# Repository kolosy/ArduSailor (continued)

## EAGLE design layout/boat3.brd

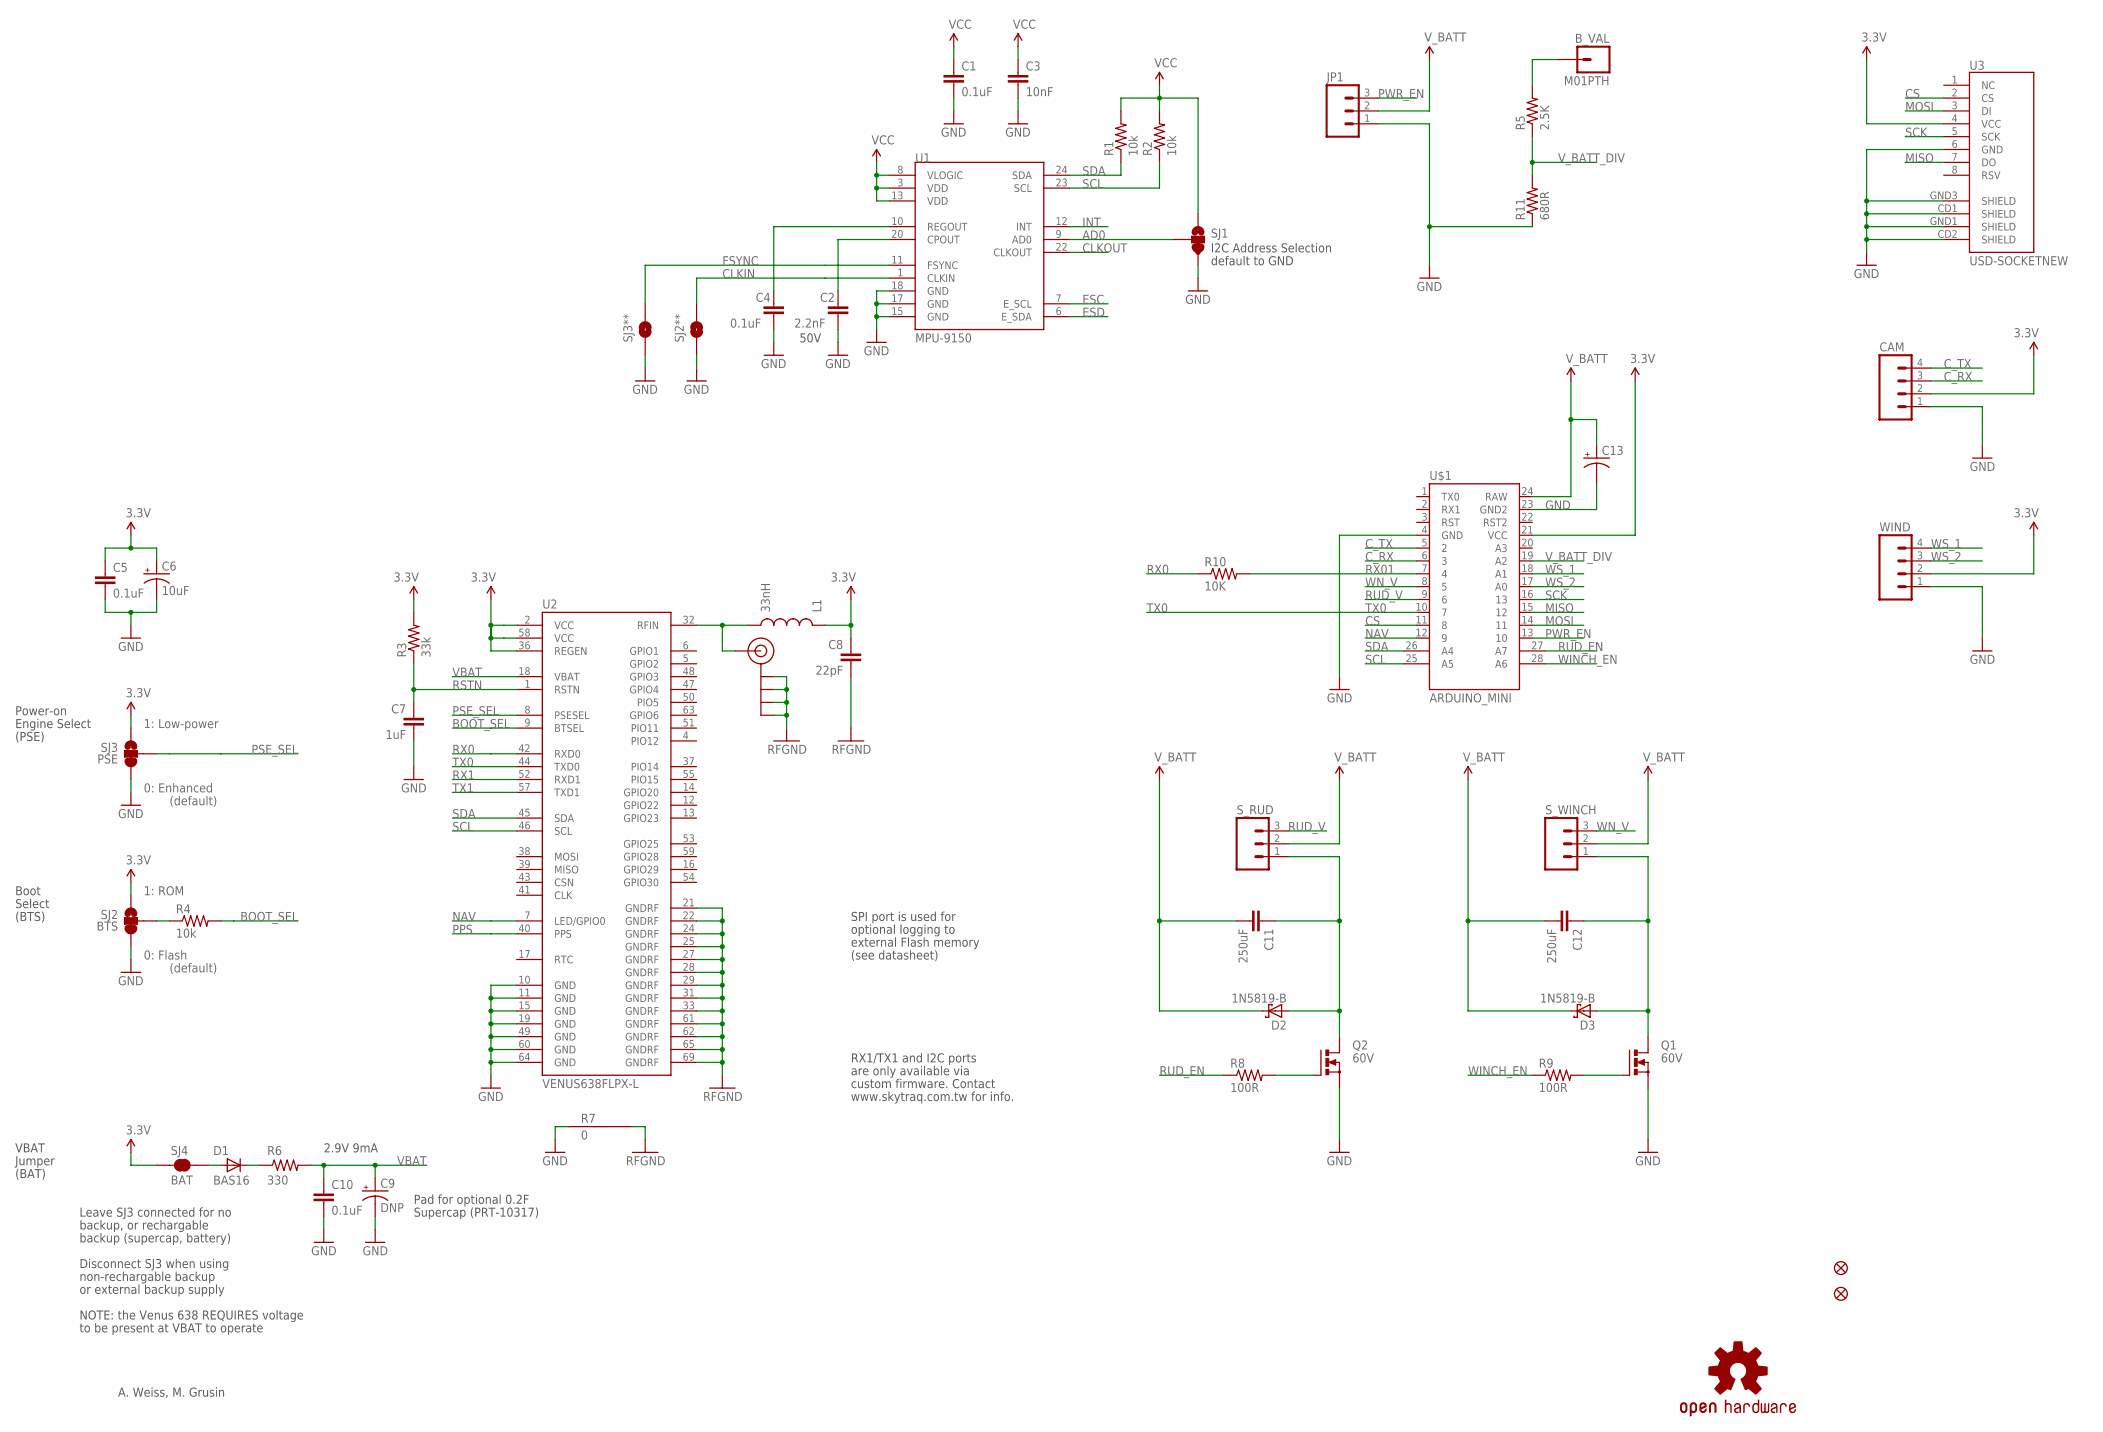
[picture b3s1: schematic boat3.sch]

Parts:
B_VAL: M01PTH; 1X01
C1, C4, C5, C10: 0.1uF; 0402-CAP
C2: 2.2nF; 0402-CAP
C3: 10nF; 0402-CAP
C6: 10uF; EIA3216
C7: 1uF; 0402-CAP
C8: 22pF; 0402-CAP
C9: DNP; CPOL-RADIAL-1000UF-25V
C11, C12: 250uF; CAP-PTH-5MM
C13: CAP_POLPTH4; CPOL-RADIAL-1000UF-25V
CAM: M04PTH; 1X04
D1: BAS16; SOD-323
D2, D3: 1N5819-B; DO41-7.6
JP1: M03SCREW; SCREWTERMINAL-3.5MM-3
JP5: SMA_EDGE; SMA-EDGE
JP7, JP8: FIDUCIALUFIDUCIAL; MICRO-FIDUCIAL
L1: 33nH; C0402
Q1, Q2: 60V; TO220BV
R1, R2, R4: 10k; 0402-RES
R3: 33k; 0402-RES
R5: 2.5K; 0603-RES
R6: 330; 0402-RES
R7: 0; GND-JUMP
R8, R9: 100R; 0603-RES
R10: 10K; 0402-RES
R11: 680R; 0603-RES
SJ1: SOLDERJUMPER_2WAYPASTE2&3; SJ_3_PASTE2&3
SJ2: BTS; SJ_3_PASTE2&3
SJ2**, SJ3**: SOLDERJUMPERTRACE; SJ_2S-TRACE
SJ3: PSE; SJ_3_PASTE2&3
SJ4: BAT; SJ_2S
S_RUD: M03PTH; 1X03
S_WINCH: M03PTH; 1X03
U1: MPU-9150; QFN-24-NP
U2: VENUS638FLPX-L; VENUS638FLPX
U3: USD-SOCKETNEW; MICRO-SD-SOCKET-PP
U$1: ARDUINO_MINI
U$4: OSHW-LOGOS; OSHW-LOGO-S
WIND: M04PTH; 1X04

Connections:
3.3V: C1.1, C3.1, C5.1, C6.A (+), C8.1, CAM.2, L1.1, R1.2, R2.2, R3.2, SJ1.1, SJ2.1, SJ3.1, SJ4.1, U1.3 (VDD), U1.8 (VLOGIC), U1.13 (VDD), U2.2 (VCC), U2.36 (REGEN), U2.58 (VCC), U3.4 (VCC), U$1.21 (VCC), WIND.2
AD0: SJ1.2, U1.9 (AD0)
ANT: JP5.SIG (SIGNAL), L1.2, U2.32 (RFIN)
BOOT_SEL: R4.2, U2.9 (BTSEL)
CLKIN: SJ2**.2, U1.1 (CLKIN)
CLKOUT: U1.22 (CLKOUT)
CS: U3.2 (CS), U$1.11 (8)
C_RX: CAM.3, U$1.6 (3)
C_TX: CAM.4, U$1.5 (2)
ESC: U1.7 (E_SCL)
ESD: U1.6 (E_SDA)
FSYNC: SJ3**.2, U1.11 (FSYNC)
GND: C1.2, C2.2, C3.2, C4.2, C5.2, C6.C (-), C7.2, C9.2 (-), C10.2, C13.2 (-), CAM.1, JP1.1, Q1.S, Q2.S, R7.1, R11.1, SJ1.3, SJ2.3, SJ2**.1, SJ3.3, SJ3**.1, U1.15 (GND), U1.17 (GND), U1.18 (GND), U2.10 (GND), U2.11 (GND), U2.15 (GND), U2.19 (GND), U2.49 (GND), U2.60 (GND), U2.64 (GND), U3.6 (GND), U3.CD1 (SHIELD), U3.CD2 (SHIELD), U3.GND1 (SHIELD), U3.GND3 (SHIELD), U$1.4 (GND), U$1.23 (GND2), WIND.1
INT: U1.12 (INT)
MISO: U3.7 (DO), U$1.15 (12)
MOSI: U3.3 (DI), U$1.14 (11)
unnamed: C2.1, U1.20 (CPOUT)
unnamed: C4.1, U1.10 (REGOUT)
unnamed: B_VAL.1, R5.2
unnamed: R4.1, SJ2.2
unnamed: D1.1 (C), R6.1
unnamed: D1.2 (A), SJ4.2
unnamed: Q2.G, R8.2
unnamed: C12.1, D3.A, Q1.D, S_WINCH.1
unnamed: C11.1, D2.A, Q2.D, S_RUD.1
unnamed: Q1.G, R9.2
NAV: U2.7 (LED/GPIO0), U$1.12 (9)
PPS: U2.40 (PPS)
PSE_SEL: SJ3.2, U2.8 (PSESEL)
PWR_EN: JP1.3, U$1.13 (10)
RFGND: C8.2, JP5.GND@0 (GND), JP5.GND@1 (GND), JP5.GND@2 (GND), JP5.GND@3 (GND), R7.2, U2.21 (GNDRF), U2.22 (GNDRF), U2.24 (GNDRF), U2.25 (GNDRF), U2.27 (GNDRF), U2.28 (GNDRF), U2.29 (GNDRF), U2.31 (GNDRF), U2.33 (GNDRF), U2.61 (GNDRF), U2.62 (GNDRF), U2.65 (GNDRF), U2.69 (GNDRF)
RSTN: C7.1, R3.1, U2.1 (RSTN)
RUD_EN: R8.1, U$1.27 (A7)
RUD_V: S_RUD.3, U$1.9 (6)
RX0: R10.1, U2.42 (RXD0)
RX1: U2.52 (RXD1)
RX01: R10.2, U$1.7 (4)
SCK: U3.5 (SCK), U$1.16 (13)
SCL: R2.1, U1.23 (SCL), U2.46 (SCL), U$1.25 (A5)
SDA: R1.1, U1.24 (SDA), U2.45 (SDA), U$1.26 (A4)
TX0: U2.44 (TXD0), U$1.10 (7)
TX1: U2.57 (TXD1)
VBAT: C9.1 (+), C10.1, R6.2, U2.18 (VBAT)
V_BATT: C11.2, C12.2, C13.1 (+), D2.C, D3.C, JP1.2, S_RUD.2, S_WINCH.2, U$1.24 (RAW)
V_BATT_DIV: R5.1, R11.2, U$1.19 (A2)
WINCH_EN: R9.1, U$1.28 (A6)
WN_V: S_WINCH.3, U$1.8 (5)
WS_1: U$1.18 (A1), WIND.4
WS_2: U$1.17 (A0), WIND.3

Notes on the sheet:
50V
I2C Address Selection
default to GND
RFGND
1: Low-power
0: Enhanced
0: Flash
1: ROM
(default)
A. Weiss, M. Grusin
Supercap (PRT-10317)
Pad for optional 0.2F
2.9V 9mA
RX1/TX1 and I2C ports
are only available via
SPI port is used for
optional logging to
external Flash memory
(see datasheet)
custom firmware. Contact
www.skytraq.com.tw for info.
Power-on
Engine Select
Boot
Select
(PSE)
(BTS)
VBAT
Jumper
(BAT)
Leave SJ3 connected for no
backup, or rechargable
backup (supercap, battery)
Disconnect SJ3 when using
non-rechargable backup
or external backup supply
NOTE: the Venus 638 REQUIRES voltage
to be present at VBAT to operate

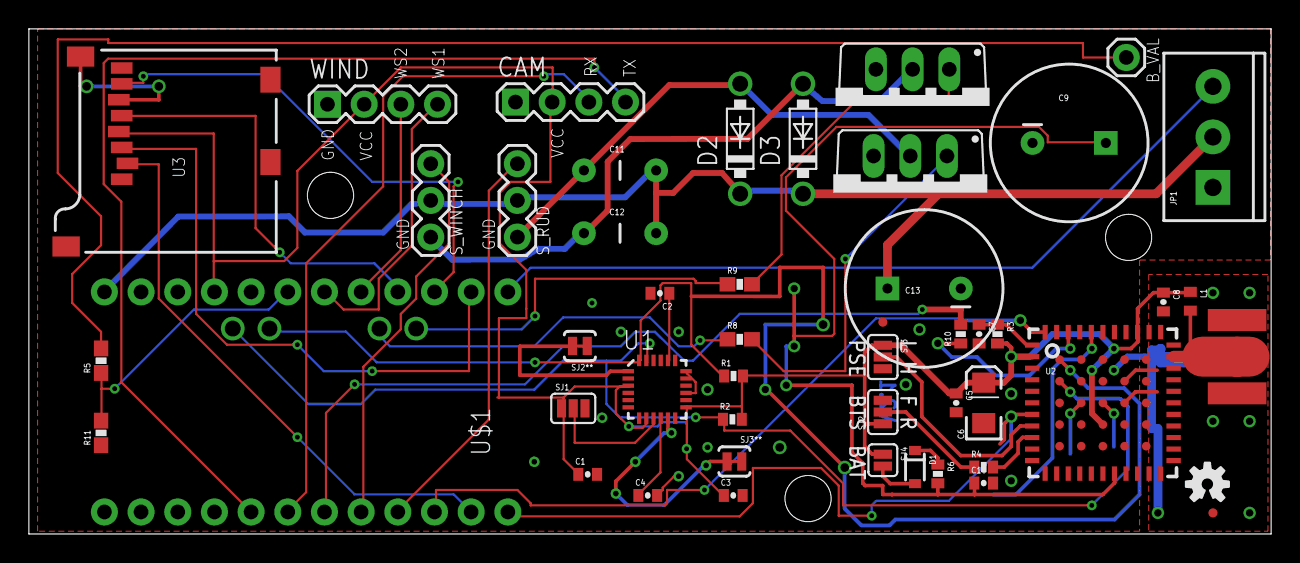
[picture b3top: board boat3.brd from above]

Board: 2 copper layers, 86.0 x 35.0 mm, 50 parts (1 on the bottom side), 42 nets.

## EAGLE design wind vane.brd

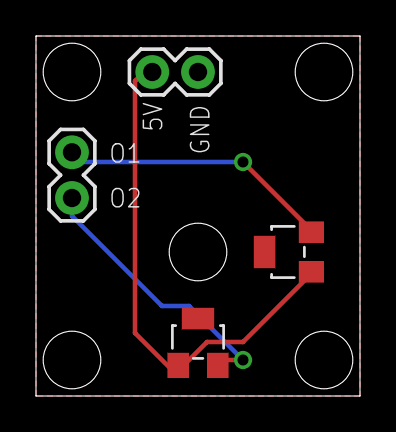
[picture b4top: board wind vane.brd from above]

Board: 2 copper layers, 18.0 x 20.0 mm, 4 parts (0 on the bottom side), 4 nets.

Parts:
IC1, IC2: A1323LH; SOT23-W
JP1, JP2: M02PTH; 1X02

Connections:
5V: IC1.1, IC2.1, JP1.2
GND: IC1.3, IC2.3, JP1.1
unnamed: IC1.2, JP2.2
unnamed: IC2.2, JP2.1

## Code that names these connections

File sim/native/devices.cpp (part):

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const double EARTH_RADIUS = 6371000;  // same as pilot.ino

// pins (firmware.ino, servo_ctl.cpp, gps.ino, wind.ino, battery.ino)
const int SP_EN = 25, RUDDER_EN = 26, WINCH_EN = 27, GPS_EN = 30, WIND_EN = 33, BATT_V_EN = 34;
const int RUDDER_PIN = 10, WINCH_PIN = 11;
const int WS1 = 8, WS2 = 9, BATT_VAL = 10;  // analog channels

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    }
    if (now >= next_fix_us) {
        next_fix_us += 1000000;
        if (pins[GPS_EN] == 0 && gps.baud > 0) gps_fix(now);
    }

    // masthead vane: follows the apparent wind with a little lag
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}

bool servo_powered(int pin) {
    int en = pin == RUDDER_PIN ? RUDDER_EN : pin == WINCH_PIN ? WINCH_EN : -1;
    return en >= 0 && pins[SP_EN] && pins[en] && servo_cmd[pin] >= 0;
}

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
int sim_analog_read(int channel) {
    if (channel == WS1 || channel == WS2) {
        if (pins[WIND_EN]) return 0;  // p-channel switch: the vane is only powered with WIND_EN low
        double a = vane + params.vane_noise * DEG * gaussian();
        double v = channel == WS1 ? 500 - VANE_RADIUS * sin(a) : 500 + VANE_RADIUS * cos(a);
        return (int)clamp(lround(v), 0, 1023);
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
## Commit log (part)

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2014-05-19 initial load
2014-05-19 cleanup
2014-05-19 more cleanup
2014-06-05 fixed word size for ahrs/wind, rotated ahrs value to match hw install, inverted wind reading, set wind offset and added gps serial start/end to fix servo issue
2014-06-05 whitespace cleanup
2014-07-22 atmega2560
2014-07-24 first pass at routing
2014-08-14 boat v5
2014-09-02 board version 5.1
2014-09-12 5.1 version final; 1A 5V reg
2014-09-17 5.1 final; submitted for build
2014-10-13 boat 5, getting ready for mega2560 firmware
2014-10-14 cleanup, porting to 2560
2015-01-29 more 3d stuff
2015-03-06 housing updates
2015-03-15 manual override mode
2015-04-30 circuit updates, firmware tweaks
2015-05-24 new calibration params, other fixes
2015-08-01 updated weather vane
2015-08-20 improvements to autopilot algorithm, less reliance on sleeps
2015-11-08 pilot tuning
2015-11-09 readme
2015-12-29 event-driven GPS stream processing, autopilot cleanup and logging improvements
2016-01-04 winch heel compensation, parameter tweaks
2016-03-06 autopilot tuning
2016-06-27 Added new servo params + GPG test
2016-08-29 Added Android controller project
2016-08-29 Cleaned up gitignore
2016-09-04 Initial usb pass
2016-09-28 Android controller updates, revised layout (v7)
2016-10-27 Finalized v7 board layout / schematic
2016-11-12 gitignore cleanup, tweaks to hw design.
2016-11-12 gitignore changes and cleanup
2016-11-14 removed blink debug stuff
2016-11-14 signing test
2016-11-14 more signging
2017-02-22 test
2017-02-22 Reverting signing test.
2017-02-22 Final verification test
2017-03-03 Added remote control operation (ability to set state by transmitting positions for rudder and winch)
2017-03-22 Working version of remote control and accompanying firmware
2017-03-26 Some cleanup in ahrs.
2017-03-26 Refactoring. Compiles but not tested.
2017-03-27 Project file cleanup
2017-03-27 Menu system! Oh, and logging from inside ahrs.cpp is b0rked.
2017-03-29 Minor cleanup, adjustment of sail winch ranges
2017-03-29 Moving steering to a PID controller
2017-03-30 Playing with PID
2017-03-30 Added tuning
2017-04-02 Cleanup, trailing averages for ahrs and wind, tweaking PID parameters
2017-04-03 Added basic trimming algo. First time out on the water with all this - moderate success!
2017-04-03 PID parameter tweak
2017-06-13 Some sample data and a c processor for understanding the logs.
2017-06-25 Fix trailing calc bug
2017-06-25 Added requested_heading to logging
2017-07-09 Got averaging for headings working
2018-05-19 new route + additional components
2018-05-28 manual motor control
2018-11-25 What appears to be a working mpu9250 compass
2018-12-11 Cleanup, relocating menu functionality into a single module
2019-11-13 Catching up
2020-03-18 Added auto-tune library for PID
2020-04-07 Added pilot debug
